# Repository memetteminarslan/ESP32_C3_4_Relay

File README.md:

# ESP32_C3_Relay_Box
This system is ann ESP32 C3 microcontroller module board designed with an LM2576 integrated circuit capable of converting input voltages ranging from 12V to 36V to a steady 5V output. The LM2576 serves as a power converter to regulate the high input voltages, allowing the ESP32 C3 microcontroller to function reliably.

The ESP32 C3 module board is equipped with WiFi and Bluetooth Low Energy (BLE) connectivity, offering low power consumption and advanced wireless capabilities. This enables easy integration into wireless networks and efficient operation in applications requiring low power consumption.

Additionally, the module board includes 6 Omron branded relays. Omron relays are used to control electrical currents, allowing for the switching or opening and closing of electrical circuits based on specific current levels. Omron's high-quality omron relays ensure reliable and durable performance.

This system supports UART or SPI serial interfaces for effective communication between the microcontroller and the relays, enabling easy monitoring and control of the relay operations.

With these features and components, this system provides an ideal solution for reliable and flexible smart home automation, industrial control, or other automation applications. Powered by the ESP32 C3 microcontroller and Omron relays, this board serves as a high-performance and versatile platform for various electronic projectss.

Bu sistem, 12V ile 36V arasındaki giriş voltajlarını sabit 5V çıkışa dönüştürebilen bir LM2576 entegre devresi ile tasarlanmış bir ESP32 C3 mikrodenetleyici modül kartıdır. LM2576, yüksek giriş voltajlarını düzenlemek için bir güç dönüştürücü olarak görev yapar ve ESP32 C3 mikrodenetleyicisinin güvenilir bir şekilde çalışmasına olanak tanır.

ESP32 C3 modül kartı, WiFi ve Bluetooth Low Energy (BLE) bağlantısı ile donatılmıştır, bu da düşük güç tüketimi ve gelişmiş kablosuz yetenekler sunar. Bu, kablosuz ağlara kolay entegrasyonu ve düşük güç tüketimi gerektiren uygulamalarda verimli çalışmayı mümkün kılar.

Ayrıca, modül kartı 6 adet Omron markalı röle içerir. Omron röleleri elektrik akımlarını kontrol etmek için kullanılır, belirli akım seviyelerine dayalı olarak elektrik devrelerinin açılması ve kapanmasına izin verir. Omron'un yüksek kaliteli röleleri güvenilir ve dayanıklı performans sağlar.

Bu sistem, mikrodenetleyici ile röleler arasında etkili iletişim için UART veya SPI seri arabirimlerini destekler, böylece röle işlemlerinin kolayca izlenmesi ve kontrol edilmesini sağlar.

Bu özellikler ve bileşenlerle bu sistem, güvenilir ve esnek akıllı ev otomasyonu, endüstriyel kontrol veya diğer otomasyon uygulamaları için ideal bir çözüm sunar. ESP32 C3 mikrodenetleyici ve Omron röleleri tarafından desteklenen bu kart, çeşitli elektronik projeler için yüksek performanslı ve çok yönlü bir platform olarak hizmet verir.

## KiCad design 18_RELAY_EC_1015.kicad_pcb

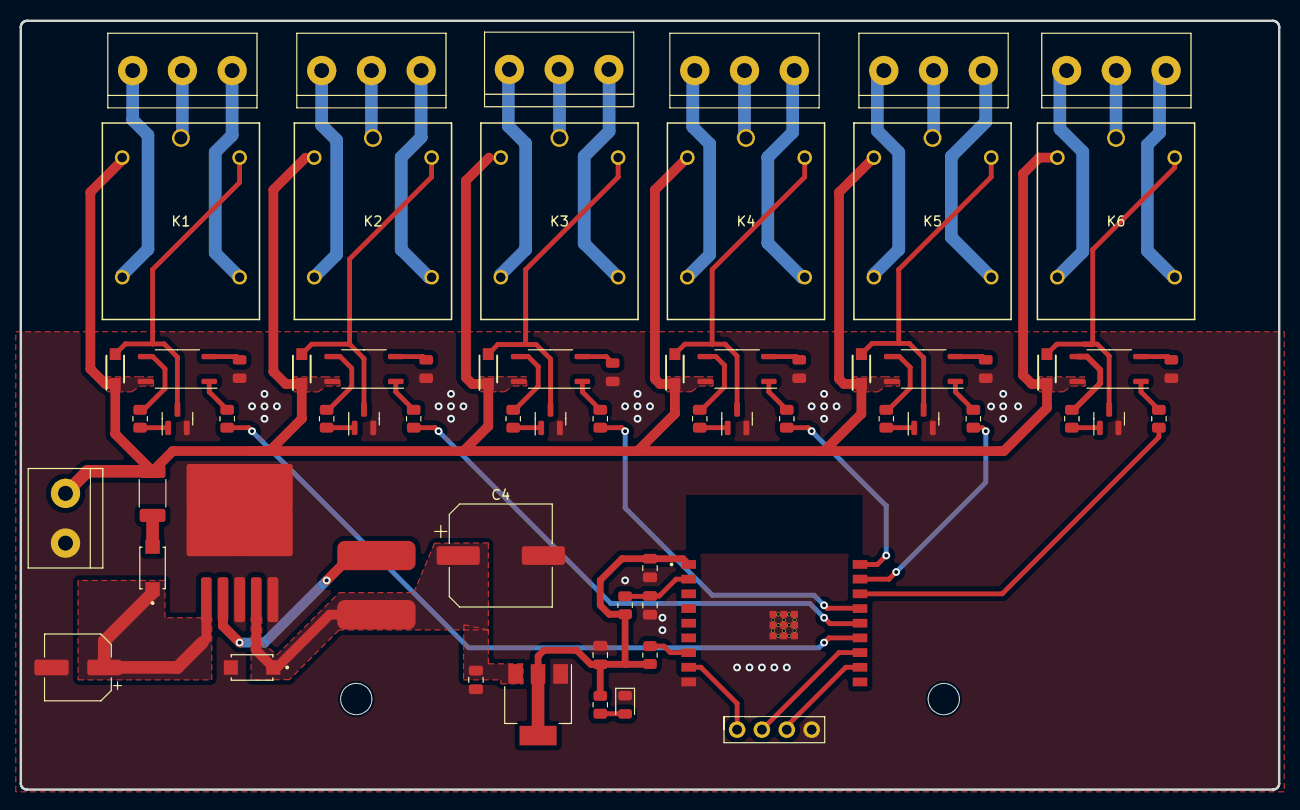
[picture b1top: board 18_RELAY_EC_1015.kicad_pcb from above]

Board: 2 copper layers, 128.5 x 78.5 mm, 69 parts (0 on the bottom side), 67 nets.

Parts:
C1, C3, C6: C; C_0805_2012Metric
C2: C_Polarized_Small; CP_Elec_6.3x7.7
C4: C_Polarized_Small; CP_Elec_10x12.6
C5: 1uF; C_0805_2012Metric
D1, D2, D3, D4, D9, D10, D14: LED; LED_0805_2012Metric
D5, D6, D7, D8, D11, D12: 1N5819W; SODFL3618X110N
D13, D15: 1N5819WS; SODFL5226X100N
F1: Fuse; Fuse_2010_5025Metric
H1, H2: MountingHole; MountingHole_3.2mm_M3
J1, J2, J3, J4, J5, J6: Screw_Terminal_01x03; TerminalBlock_bornier-3_P5.08mm
J7: Screw_Terminal_01x02; TerminalBlock_bornier-2_P5.08mm
J8: Conn_01x04_Male; PinSocket_1x04_P2.54mm_Vertical
K1, K2, K3, K4, K5, K6: G5LE-1-DC24; RELAY_G5LA_OMR
L1: L; 100uH
Q1, Q2, Q3, Q4, Q5, Q6: BC817; SOT-23
R1, R2, R3, R4, R9, R10: 220r; R_0805_2012Metric
R5, R6, R7, R8, R11, R12: 1k; R_0805_2012Metric
R13: R; R_0805_2012Metric
R14: 10k; R_0805_2012Metric
R17: 10K; R_0805_2012Metric
U1, U2, U3, U4, U5, U6: TLP185; SOIC-4_4.55x3.7mm_P2.54mm
U7: AMS1117-3.3; SOT-223-3_TabPin2
U8: LM2576HVS-5; TO-263-5_TabPin3
U9: ESP32-C3-WROOM-02-N4; MODULE_ESP32-C3-WROOM-02-H4

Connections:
+3V3: C3.1, C6.1, R13.1, R14.1, R17.1, U7.2 (VO), U9.1 (3V3)
+5V: C1.1, C4.1, D15.1 (K), L1.2, U7.3 (VI), U8.4 (FB)
+24V: D5.1 (K), D6.1 (K), D7.1 (K), D8.1 (K), D11.1 (K), D12.1 (K), F1.1, J7.2, K1.2 (COIL_1), K2.2 (COIL_1), K3.2 (COIL_1), K4.2 (COIL_1), K5.2 (COIL_1), K6.2 (COIL_1), U1.6, U2.6, U3.6, U4.6, U5.6, U6.6
EN: C5.1, R17.2, U9.2 (EN)
GND: C1.2, C2.2, C3.2, C4.2, C5.2, C6.2, D1.1 (K), D2.1 (K), D3.1 (K), D4.1 (K), D9.1 (K), D10.1 (K), D14.1 (K), D15.2 (A), J7.1, J8.4, Q1.2 (E), Q2.2 (E), Q3.2 (E), Q4.2 (E), Q5.2 (E), Q6.2 (E), U7.1 (GND), U8.3 (GND), U8.5 (~ON/OFF), U9.9 (GND), U9.19 (GND), U9.20 (GND), U9.21 (GND), U9.22 (GND), U9.23 (GND), U9.24 (GND), U9.25 (GND), U9.26 (GND), U9.27 (GND), U9.28 (GND), U9.29 (GND), U9.30 (GND), U9.31 (GND), U9.32 (GND), U9.33 (GND), U9.34 (GND), U9.35 (GND), U9.36 (GND), U9.37 (GND), U9.38 (GND), U9.39 (GND)
IO8: R14.2, U9.7 (IO8)
IO9: J8.1, U9.8 (IO9)
unnamed: D1.2 (A), U1.3
unnamed: D2.2 (A), U2.3
unnamed: D3.2 (A), U3.3
unnamed: D4.2 (A), U4.3
unnamed: D5.2 (A), K1.5 (COIL_2), Q1.3 (C)
unnamed: D6.2 (A), K2.5 (COIL_2), Q2.3 (C)
unnamed: D7.2 (A), K3.5 (COIL_2), Q3.3 (C)
unnamed: D8.2 (A), K4.5 (COIL_2), Q4.3 (C)
unnamed: D9.2 (A), U5.3
unnamed: D10.2 (A), U6.3
unnamed: D11.2 (A), K6.5 (COIL_2), Q5.3 (C)
unnamed: D12.2 (A), K5.5 (COIL_2), Q6.3 (C)
unnamed: D13.2 (A), F1.2
unnamed: C2.1, D13.1 (K), U8.1 (VIN)
unnamed: D14.2 (A), R13.2
unnamed: J1.1, K1.3 (NO)
unnamed: J1.2, K1.1 (COM)
unnamed: J1.3, K1.4 (NC)
unnamed: J2.1, K2.3 (NO)
unnamed: J2.2, K2.1 (COM)
unnamed: J2.3, K2.4 (NC)
unnamed: J3.1, K3.3 (NO)
unnamed: J3.2, K3.1 (COM)
unnamed: J3.3, K3.4 (NC)
unnamed: J4.1, K4.3 (NO)
unnamed: J4.2, K4.1 (COM)
unnamed: J4.3, K4.4 (NC)
unnamed: J5.1, K5.3 (NO)
unnamed: J5.2, K5.1 (COM)
unnamed: J5.3, K5.4 (NC)
unnamed: J6.1, K6.3 (NO)
unnamed: J6.2, K6.1 (COM)
unnamed: J6.3, K6.4 (NC)
unnamed: Q1.1 (B), R5.2
unnamed: Q2.1 (B), R6.2
unnamed: Q3.1 (B), R7.2
unnamed: Q4.1 (B), R8.2
unnamed: Q5.1 (B), R11.2
unnamed: Q6.1 (B), R12.2
unnamed: R1.2, U1.1
unnamed: R2.2, U2.1
unnamed: R3.2, U3.1
unnamed: R4.2, U4.1
unnamed: R5.1, U1.4
unnamed: R6.1, U2.4
unnamed: R7.1, U3.4
unnamed: R8.1, U4.4
unnamed: R9.2, U5.1
unnamed: R10.2, U6.1
unnamed: R11.1, U5.4
unnamed: R12.1, U6.4
unnamed: L1.1, U8.2 (OUT)
RLY01: R1.1, U9.13 (IO18)
RLY02: R2.1, U9.14 (IO19)
RLY03: R3.1, U9.15 (IO3)
RLY04: R4.1, U9.18 (IO0)
RLY05: R10.1, U9.17 (IO1)
RLY06: R9.1, U9.16 (IO2)
RX: J8.3, U9.11 (RXD)
TX: J8.2, U9.12 (TXD)

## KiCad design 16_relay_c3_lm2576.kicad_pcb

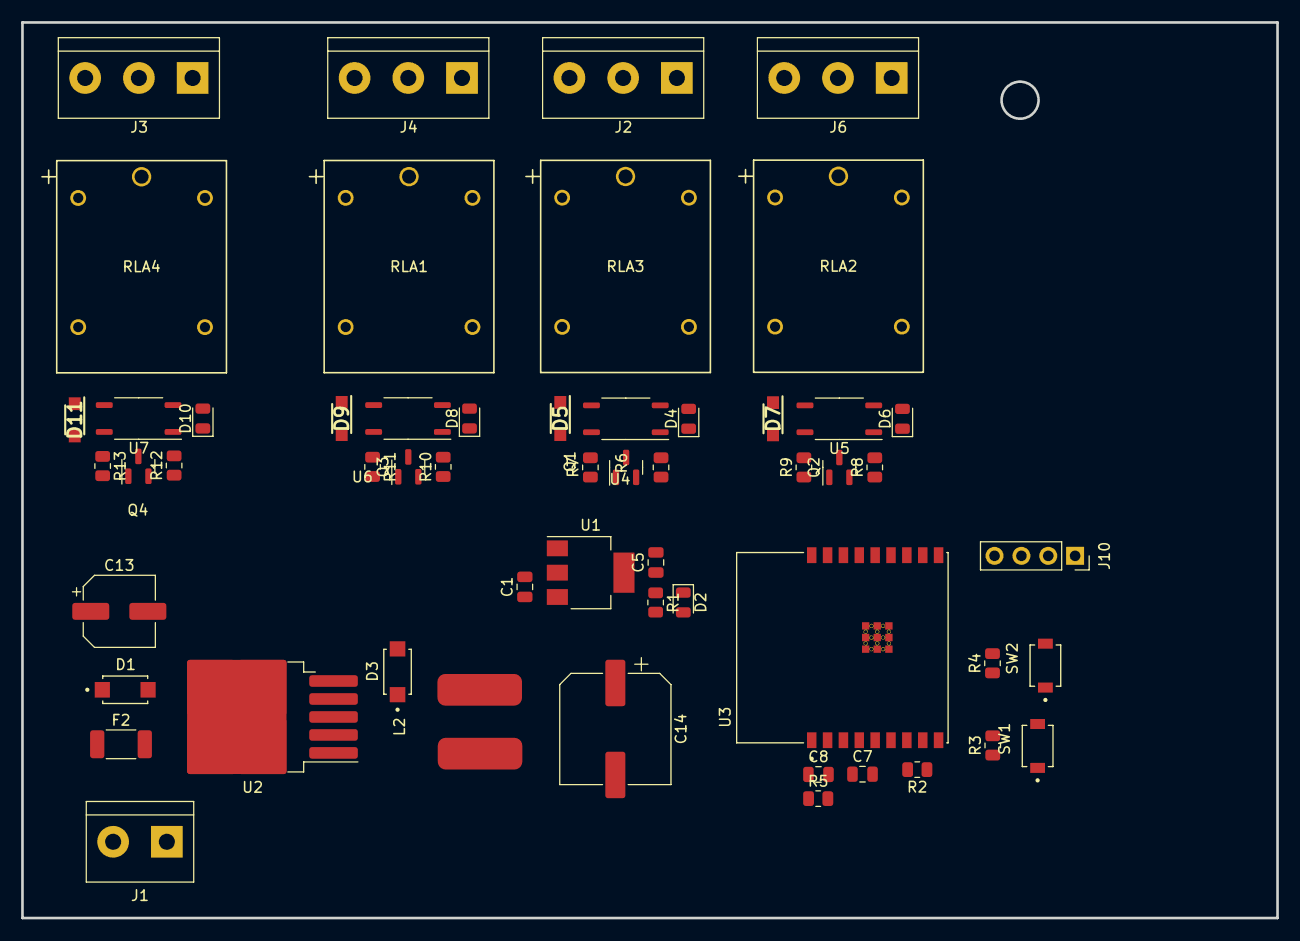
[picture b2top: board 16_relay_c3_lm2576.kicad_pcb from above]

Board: 2 copper layers, 118.7 x 84.7 mm, 55 parts (0 on the bottom side), 51 nets, no tracks yet.

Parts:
C1, C5, C8: C; C_0805_2012Metric
C7: 1uF; C_0805_2012Metric
C13: C_Polarized_Small; CP_Elec_6.3x7.7
C14: C_Polarized_Small; CP_Elec_10x12.6
D1, D3: 1N5819WS; SODFL5226X100N
D2, D4, D6, D8, D10: LED; LED_0805_2012Metric
D5, D7, D9, D11: 1N5819W; SODFL3618X110N
F2: Fuse; Fuse_2010_5025Metric
J1: Screw_Terminal_01x02; TerminalBlock_bornier-2_P5.08mm
J2, J3, J4, J6: Screw_Terminal_01x03; TerminalBlock_bornier-3_P5.08mm
J10: Conn_01x04_Male; PinSocket_1x04_P2.54mm_Vertical
L2: L; 100uH
Q1, Q2, Q3, Q4: BC817; SOT-23
R1, R3, R4: R; R_0805_2012Metric
R2: 10k; R_0805_2012Metric
R5: 10K; R_0805_2012Metric
R6, R8, R10, R12: 220r; R_0805_2012Metric
R7, R9, R11, R13: 1k; R_0805_2012Metric
RLA1, RLA2, RLA3, RLA4: G5LA-1 DC12; RELAY_G5LA_OMR
SW1, SW2: SW_Push; SW_TL1015AF160QG
U1: AMS1117-3.3; SOT-223-3_TabPin2
U2: LM2576HVS-5; TO-263-5_TabPin3
U3: ESP32-C3-WROOM-02-N4; MODULE_ESP32-C3-WROOM-02-H4
U4, U5, U6, U7: TLP185; SOIC-4_4.55x3.7mm_P2.54mm

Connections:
+3V3: C5.1, C8.1, R1.1, R2.1, R5.1, U1.2 (VO), U3.1 (3V3)
+5V: C1.1, C14.1, D3.1 (K), L2.2, U1.3 (VI), U2.4 (FB)
+24V: D5.1 (K), D7.1 (K), D9.1 (K), D11.1 (K), F2.1, J1.2, RLA1.5, RLA2.5, RLA3.5, RLA4.5, U4.6, U5.6, U6.6, U7.6
EN: C7.1, R3.1, R5.2, U3.2 (EN)
GND: C1.2, C5.2, C7.2, C8.2, C13.2, C14.2, D2.1 (K), D3.2 (A), D4.1 (K), D6.1 (K), D8.1 (K), D10.1 (K), J1.1, J10.4, Q1.2 (E), Q2.2 (E), Q3.2 (E), Q4.2 (E), SW1.2, SW2.2, U1.1 (GND), U2.3 (GND), U2.5 (~ON/OFF), U3.9 (GND), U3.19 (GND), U3.20 (GND), U3.21 (GND), U3.22 (GND), U3.23 (GND), U3.24 (GND), U3.25 (GND), U3.26 (GND), U3.27 (GND), U3.28 (GND), U3.29 (GND), U3.30 (GND), U3.31 (GND), U3.32 (GND), U3.33 (GND), U3.34 (GND), U3.35 (GND), U3.36 (GND), U3.37 (GND), U3.38 (GND), U3.39 (GND)
IO8: R2.2, U3.7 (IO8)
IO9: J10.3, R4.1, U3.8 (IO9)
unnamed: D1.2 (A), F2.2
unnamed: C13.1, D1.1 (K), U2.1 (VIN)
unnamed: D2.2 (A), R1.2
unnamed: D4.2 (A), U4.3
unnamed: D5.2 (A), Q1.3 (C), RLA3.1
unnamed: D6.2 (A), U5.3
unnamed: D7.2 (A), Q2.3 (C), RLA2.1
unnamed: D8.2 (A), U6.3
unnamed: D9.2 (A), Q3.3 (C), RLA1.1
unnamed: D10.2 (A), U7.3
unnamed: D11.2 (A), Q4.3 (C), RLA4.1
unnamed: J2.1, RLA3.4
unnamed: J2.2, RLA3.3
unnamed: J2.3, RLA3.2
unnamed: J3.1, RLA4.4
unnamed: J3.2, RLA4.3
unnamed: J3.3, RLA4.2
unnamed: J4.1, RLA1.4
unnamed: J4.2, RLA1.3
unnamed: J4.3, RLA1.2
unnamed: J6.1, RLA2.4
unnamed: J6.2, RLA2.3
unnamed: J6.3, RLA2.2
unnamed: Q1.1 (B), R7.2
unnamed: Q2.1 (B), R9.2
unnamed: Q3.1 (B), R11.2
unnamed: Q4.1 (B), R13.2
unnamed: R3.2, SW1.1
unnamed: R4.2, SW2.1
unnamed: R6.2, U4.1
unnamed: R7.1, U4.4
unnamed: R8.2, U5.1
unnamed: R9.1, U5.4
unnamed: R10.2, U6.1
unnamed: R11.1, U6.4
unnamed: R12.2, U7.1
unnamed: R13.1, U7.4
unnamed: L2.1, U2.2 (OUT)
RLY01: R6.1, U3.18 (IO0)
RLY02: R8.1, U3.17 (IO1)
RLY03: R10.1, U3.16 (IO2)
RLY04: R12.1, U3.15 (IO3)
RX: J10.2, U3.11 (RXD)
TX: J10.1, U3.12 (TXD)
